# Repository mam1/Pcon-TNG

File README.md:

## PCON-TNG
------
### *** under construction and not stable ***
------
These are my notes on developing a multi channel programmable HVAC controller. The current iteration of the system is comprised of several ESP8266 modules, a BeagleBone Black (BBB), a BBB custom Control Cape and Digital IO Board(s) from Parallax. The system supports 16 channels.

A daemon (Dcon) is started as part of the boot process of the BeagleBone. The daemon decides if a channel should be on or off.  It does this by looking at a memory mapped file (ipc.dat). The memory mapped file creates a persistent space in virtual memory allowing processes to communicate.  It is maintained by a user interface process (Pcon).  Pcon is only active when a user is interacting with the system.  Temperature and humidity data is collected by ESP8266 modules. The ESP8266 modules read HDT22 sensors and use a wireless connection to post the data to the cloud (ThingSpeak) and to an Apache sever running on the BBB. A CGI on the BBB makes the data available to the daemon by updating shared memory and posts the data to a SQL database running on the Linux development machine.

A channel can be controlled by:

* time of day
* time of day and a sensor value
* manually

The BBB Control Cape (part of this project) maps 16 BeagleBone gpio pins to 2 2x10 pin headers.  Each header can drive 1 Parallax Digital IO board (DIOB).  It also connects 4 gpio pins to a heart beat display on the cape.

The Pcon application runs on the BBB.  It interacts with the daemon using shared memory.  Pcon provides a state machine driven user interface to configure channels, build and maintain schedules, query sensor and channel data, manually control channel states, etc.
- - - - - - - - -
#### Hardware
  * **BeagleBone Black Rev C - 4GB Flash, adafruit**
  * **BBB Control Cape**
    *  2 - 2 x 10 headers, DIOB control
            * Digital IO Board (DIOB), Sharp solid state relays part# S202S02F, Parallax
    *  4 - heart beat leds
  * **Wireless Sensors**
    * ESP8266 NodeMCU Dev Board, R2, Electro Dragon
    * DHT22 temperature/humidity sensor, Electro Dragon
    * 0.96” 128*64 OLED Display (i2c), Electro Dragon

##### BeagleBone GPIO assignments
                           {header,pin,gpio}
    * #define _CHAN0          {8,27,86}
    * #define _CHAN1          {8,28,88}
    * #define _CHAN2          {8,29,87}
    * #define _CHAN3          {8,30,89}
    * #define _CHAN4          {8,31,10}
    * #define _CHAN5          {8,32,11}
    * #define _CHAN6          {8,33,9}
    * #define _CHAN7          {8,34,81}
    * #define _CHAN8          {8,35,8}
    * #define _CHAN9          {8,36,80}
    * #define _CHAN10         {8,37,78}
    * #define _CHAN11         {8,38,79}
    * #define _CHAN12         {8,39,76}
    * #define _CHAN13         {8,40,77}
    * #define _CHAN14         {8,41,74}
    * #define _CHAN15         {8,42,75}
    * #define _HB0            {8,43,72}
    * #define _HB1            {8,44,73}
    * #define _HB2            {8,45,70}
    * #define _HB3            {8,46,71}

##### Parallel connection between BBB and DIOB(s)

#### Development Environment:

All code is stored on github.  The repository is cloned on two development machines.  At one site I have a Linux box running Mint 18.x and at the other I have have an iMac running OS X 10.10.x . The Bone is connected to my network. I can access it from either site using ssh. My makefiles use rsync to move the binaries from the development machines to the Bone as part of the build process. 

When cross compiling for the Bone on OS X I am using a tool chain I got from http://will-tm.com/cross-compiling-mac-os-x-mavericks. The only thing I needed to do was to create a case sensitive partition before copying the files from the .dmg file.  On the Linux box I tried installing a cross compile tool chain using the Mint software manager and experienced a lot of problems. After spending a lot of time dealing with missing files I gave up and installed the linaro-arm-linux-gnueabihf-4.9-2014.09_linux tool chain and it worked on the first try.

#### Language
* C - BBB
* Lua - ESP8266
* Bash Script
* Make

#### Envirnoment
* Development machines
	*	Mint 18.x - Intel Core i5-6600K 3.5GHz Quad-Core, Asus Z170-A ATX LGA1151 Motherboard Processor
	*	OS X 10.11.x - 3.4 GHz Intel Core i7 (iMac)
* BeagleBone Black (rev C)- Debian, jessie
* ESP8266 (nodeMCU dev board r2) - nodeMCU firmware 
* Communication
    *   MQTT broker (mosquitto) running on the BeagleBone

#### Channels and Schedules 
A channel is controlled by a schedule. There is a different schedule for each day of the week. Each channel has it own set of schedules. Channels 0-7 can switch a 60 volt 1.1 amp loads.  Channels 8 -15 can switch 120 volt 8 amp loads.  Each channel can be set manually to on or off.  Channels and also be controlled by time of day, i.e. on at 8:00 off at 14:30 or sensor value and time.  When a channel is controlled by time and sensor once a minute the remote sensor value is compared to the value stored in the schedule for current time and day of the week. If the actual values exceeds the schedule value the channel is turned off when. If the schedule values is less than the actual value the channel is turned on.  

##### Schedules:
A schedule is a list of times and corresponding states.  A channel that is controlled by time will be a list of times and states.  For example, a schedule of:

* 1:00  on
* 13:00 off

will result in the channel turning on at 1:00AM and off at 1:00PM.  If the current time is between 13:00 and 24:00 or between 0:0 and 13:00 the channel will be off.  Between 1:00 and 13:00 it will be on. While a schedule of:

* 1:00  off
* 13:00 on 

will result in the channel being off between 1:00 - 13:00. It will be on at any time before 1:00 or after 13:00.

* 1:00  on
* 13:00 off
* 18:00 on

will result in the channel turning on at 1:00, off at 13:00 and on at 18:00.  If the current time is between 1:00 and 13:00 the channel will be on, between 13:00 and 18:00 it will be off, between 18:00 and 0:0 it will be on and between 0:0 and 13:00 it will also be on.

#### MQTT
##### Topic structure:
topic = location1/location2/location3/command|sensor|status/text|float

#### Application Architecture
##### Interprocess Communication (BBB)
A memory mapped file is used to create a shared memory space in virtual memory.  This file contains communication, system, schedule and sensor data.  A daemon is started as part of the boot process on the BBB. If the daemon does not find the file it creates and initializes it.  Other processes can access this shared memory space.  Semaphores are used to control access to shared memory.
##### Processes
A daemon (Dcon) running on the BBB communicates with the DIOB(s).  It uses data located in a memory mapped file (ipc.dat) and the real time clock to determine the state of each channel. The state of each channel is reset once every minute. The daemon does not require any other processes to be active.

A second daemon (mqtt-watcher) running on the BBB connects to a mqtt broker also running on the BBB.  The daemon subscribes to a high level topic and listens for any message.  It parses the topic and takes appropriate action.

A command processor (Pcon) is the user interface to the system.  It allows the user to modify the data in shared memory.

ESP8266 modules run independently of other system components.  Each module posts its sensor readings to an Apache web server running on the BBB.  A CGI (Scon) loads the readings into  shared memory. 
##### Command Processor
The command processor is the most complex part of this project. 

The use of unbuffered input allows the application to mediately react to the press of the ECS key, but it requires that the command processor handle the arrow and delete keys. The command processor maintains a buffer which matches the user's screen. The process loops waiting for a character to be detected.  ESC, Del, up_arrow, down_arrow, left_arrow and right_arrow are handled directly.  An ESC will clear all buffers and reset both state machines.  The delete and arrow commands work as they do on the command line. Any other character is passed to the first state machine (char_fsm).  It parses the input stream into tokens and pushes them on to FIFO stack.  A CR will cause char_fsm to pass the stack of tokes to the command processor.  

The command processor pops tokens off the stack and feeds them to a second fsm (cmd_fsm).  It takes some action based on the token.  If more input is required it is popped off the stack, if present, or the user is prompted. This continues until the stack is empty. Then the command processor lets the cms_fsm know there is no more input then continues the main loop, waiting for user input. 

When the main event loop detects a non-empty token stack it passes the stack to a second state machine (cmd_fsm) which processes the token stack.

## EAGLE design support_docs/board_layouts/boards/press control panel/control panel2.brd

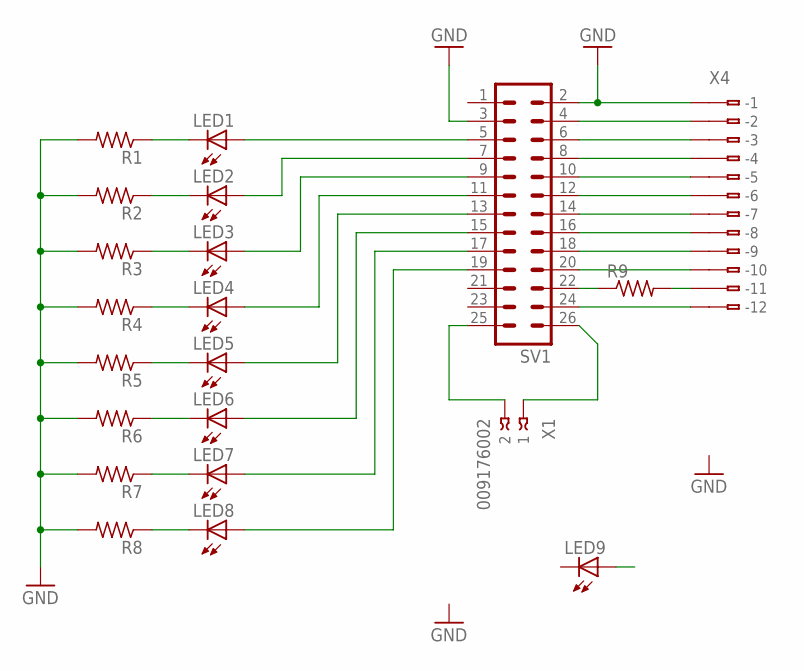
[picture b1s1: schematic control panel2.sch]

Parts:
LED1, LED2, LED3, LED4, LED5, LED6, LED7, LED8, LED9: LED3MM
R1, R2, R3, R4, R5, R6, R7, R8: R-US_0309/V; 0309V
R9: R-US_0204/7; 0204/7
SV1: MA13-2
X1: 009176002
X4: 233-212

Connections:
GND: R1.2, R2.2, R3.2, R4.2, R5.2, R6.2, R7.2, R8.2, SV1.2, SV1.3, X4.B1 (B-1)
unnamed: LED1.A, SV1.5
unnamed: LED2.A, SV1.7
unnamed: LED3.A, SV1.9
unnamed: LED4.A, SV1.11
unnamed: LED5.A, SV1.13
unnamed: LED6.A, SV1.15
unnamed: LED7.A, SV1.17
unnamed: LED8.A, SV1.19
unnamed: LED1.K (C), R1.1
unnamed: LED2.K (C), R2.1
unnamed: LED3.K (C), R3.1
unnamed: LED4.K (C), R4.1
unnamed: LED5.K (C), R5.1
unnamed: LED6.K (C), R6.1
unnamed: LED7.K (C), R7.1
unnamed: LED8.K (C), R8.1
unnamed: SV1.24, X4.B12 (B-12)
unnamed: SV1.4, X4.B2 (B-2)
unnamed: SV1.6, X4.B3 (B-3)
unnamed: SV1.8, X4.B4 (B-4)
unnamed: SV1.10, X4.B5 (B-5)
unnamed: SV1.12, X4.B6 (B-6)
unnamed: SV1.14, X4.B7 (B-7)
unnamed: SV1.16, X4.B8 (B-8)
unnamed: SV1.25, X1.2
unnamed: SV1.26, X1.1
unnamed: SV1.18, X4.B9 (B-9)
unnamed: SV1.20, X4.B10 (B-10)
unnamed: R9.1, SV1.22
unnamed: R9.2, X4.B11 (B-11)

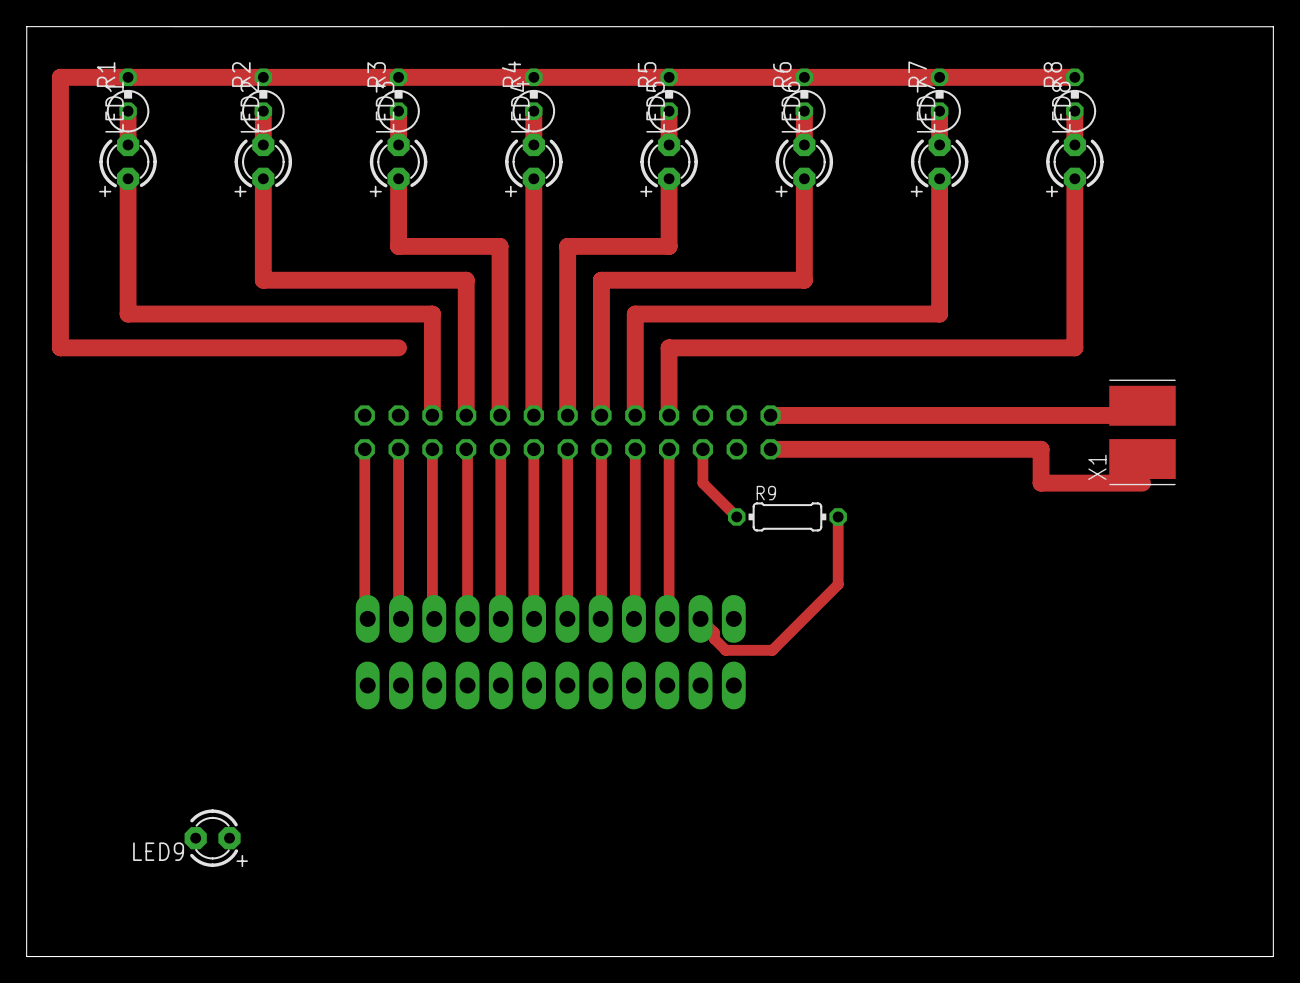
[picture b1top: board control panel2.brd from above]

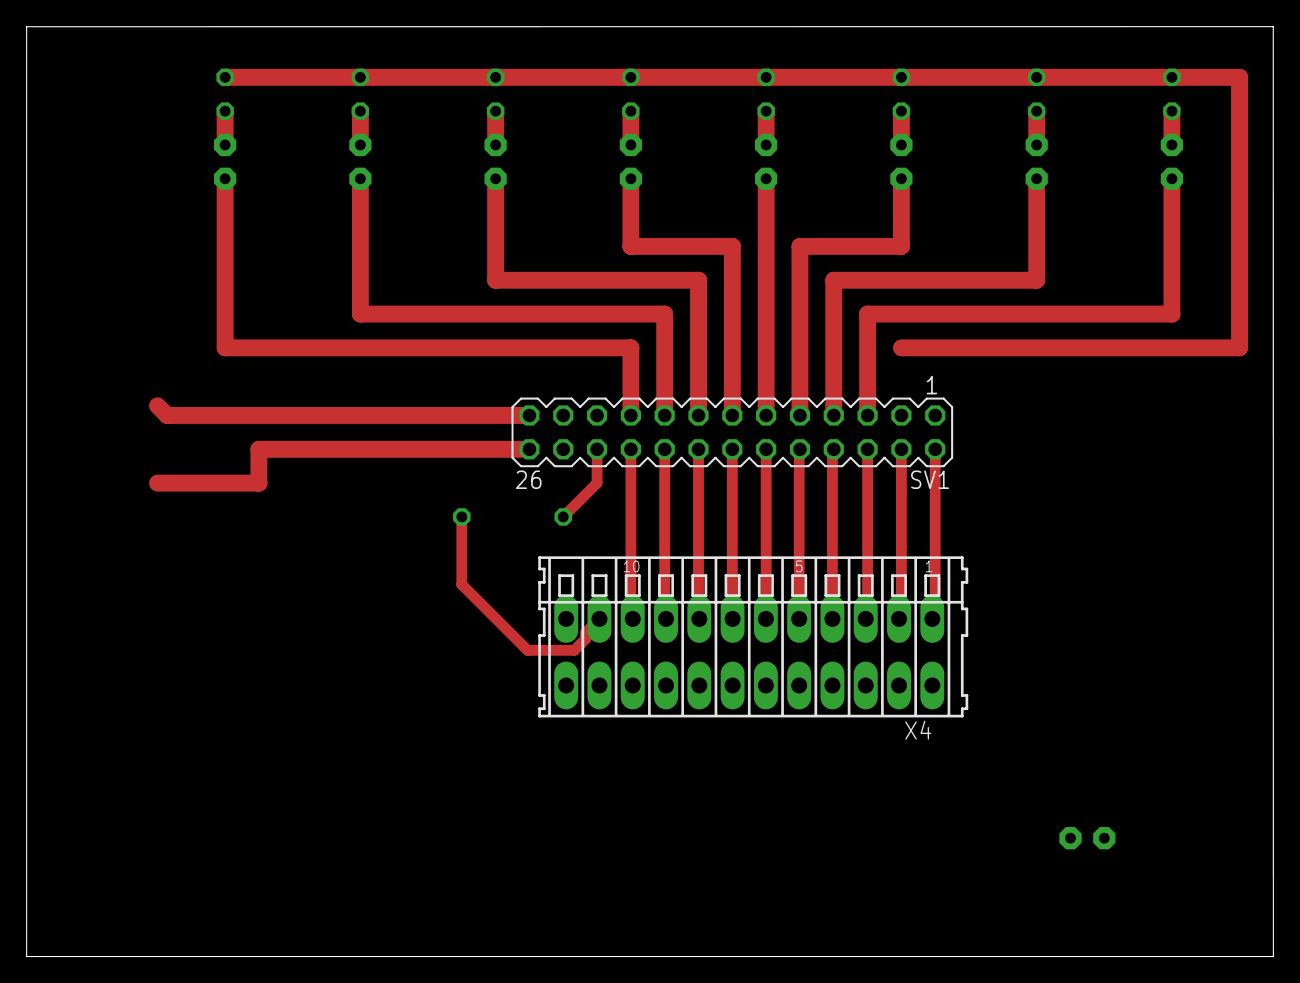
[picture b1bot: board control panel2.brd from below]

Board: 2 copper layers, 93.7 x 69.9 mm, 21 parts (2 on the bottom side), 31 nets.

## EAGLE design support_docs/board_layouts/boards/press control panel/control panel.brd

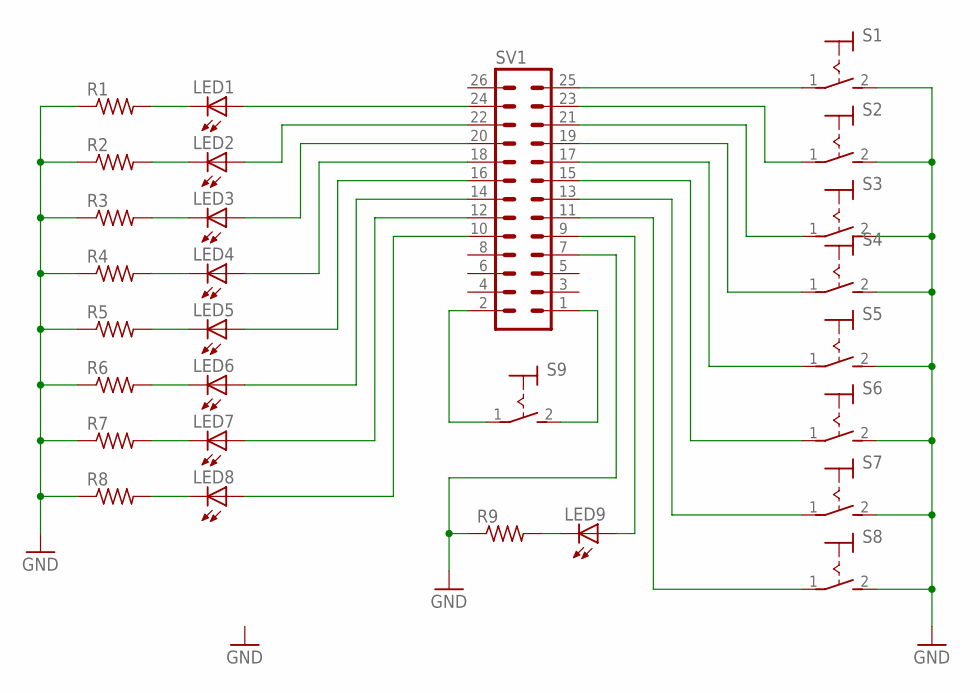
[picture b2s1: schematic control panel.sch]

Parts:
LED1, LED2, LED3, LED4, LED5, LED6, LED7, LED8, LED9: LED3MM
R1, R2, R3, R4, R5, R6, R7, R8, R9: R-US_0309/12; 0309/12
S1, S2, S3, S4, S5, S6, S7, S8, S9: MS243
SV1: MA13-2

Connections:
GND: R1.1, R2.1, R3.1, R4.1, R5.1, R6.1, R7.1, R8.1, R9.1, S1.2 (S), S2.2 (S), S3.2 (S), S4.2 (S), S5.2 (S), S6.2 (S), S7.2 (S), S8.2 (S), SV1.7, SV1.8
unnamed: LED1.A, SV1.24
unnamed: LED2.A, SV1.22
unnamed: LED3.A, SV1.20
unnamed: LED4.A, SV1.18
unnamed: LED5.A, SV1.16
unnamed: LED6.A, SV1.14
unnamed: LED7.A, SV1.12
unnamed: LED8.A, SV1.10
unnamed: LED1.K (C), R1.2
unnamed: LED2.K (C), R2.2
unnamed: LED3.K (C), R3.2
unnamed: LED4.K (C), R4.2
unnamed: LED5.K (C), R5.2
unnamed: LED6.K (C), R6.2
unnamed: LED7.K (C), R7.2
unnamed: LED8.K (C), R8.2
unnamed: S1.1, SV1.25
unnamed: S2.1, SV1.23
unnamed: S3.1, SV1.21
unnamed: S4.1, SV1.19
unnamed: S5.1, SV1.17
unnamed: S6.1, SV1.15
unnamed: S7.1, SV1.13
unnamed: S8.1, SV1.11
unnamed: S9.1, SV1.2
unnamed: S9.2 (S), SV1.1
unnamed: LED9.A, SV1.9
unnamed: LED9.K (C), R9.2

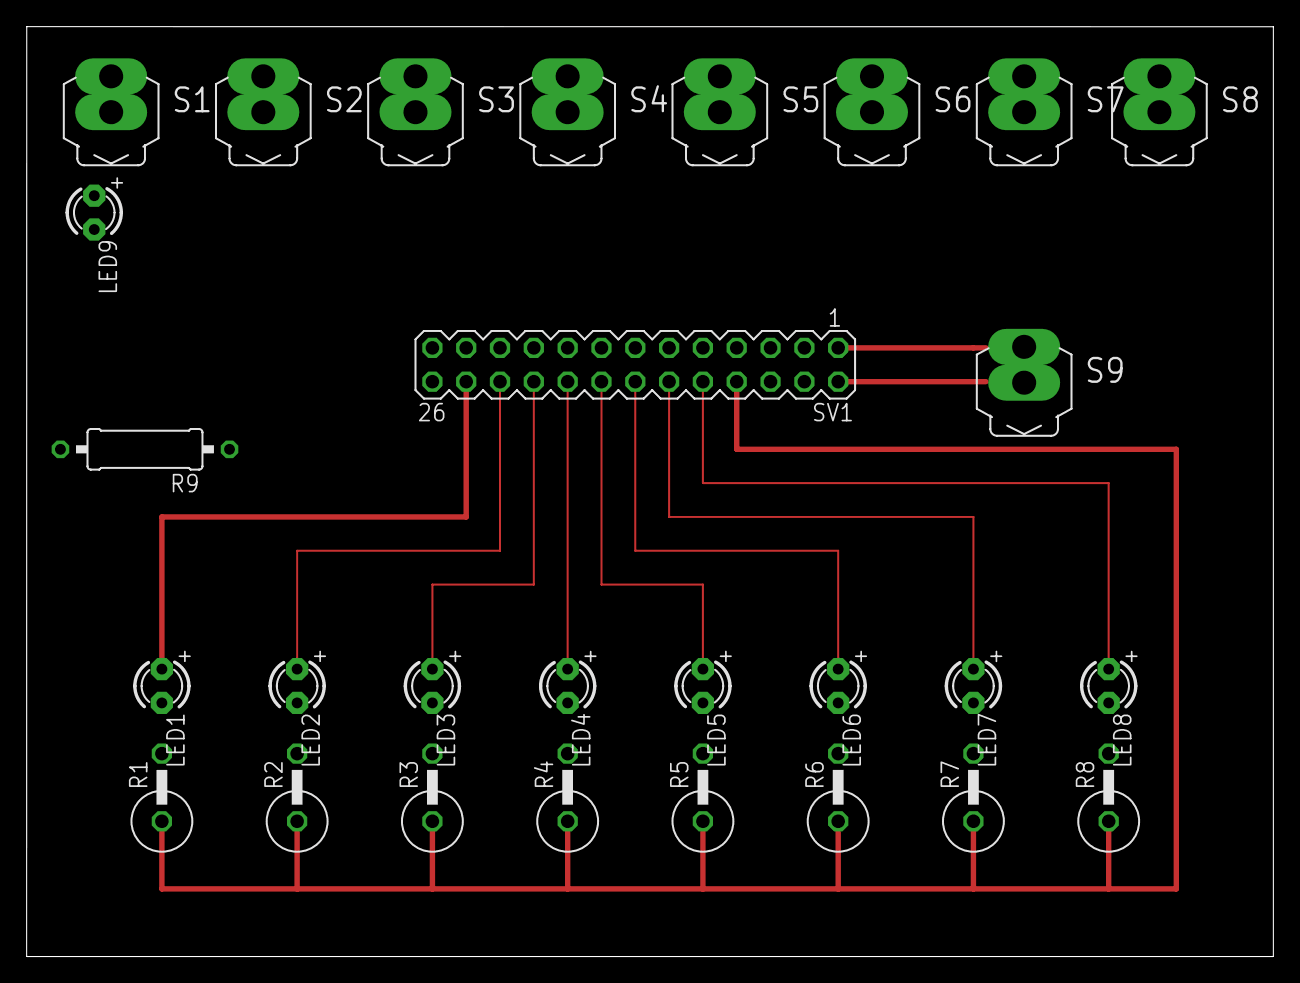
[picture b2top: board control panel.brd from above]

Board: 2 copper layers, 93.7 x 69.9 mm, 28 parts (0 on the bottom side), 29 nets.

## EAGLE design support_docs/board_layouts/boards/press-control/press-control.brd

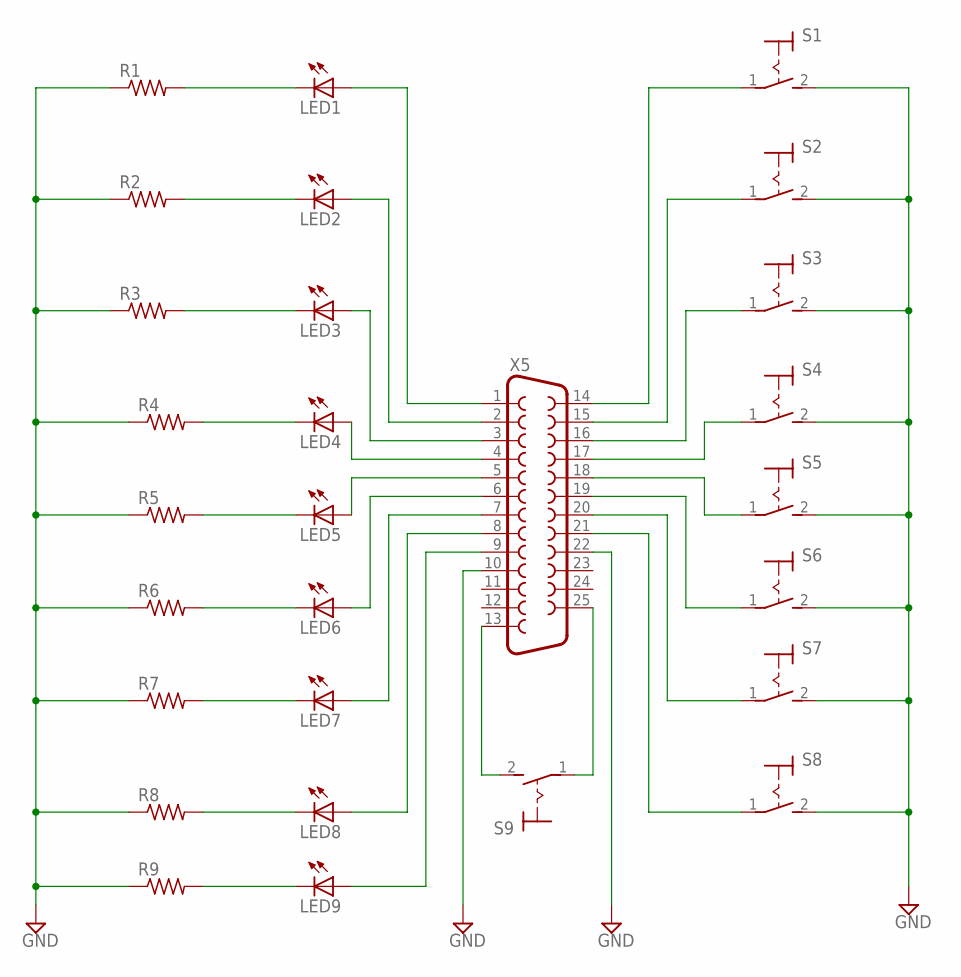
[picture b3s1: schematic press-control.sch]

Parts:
LED1, LED2, LED3, LED4, LED5, LED6, LED7, LED8, LED9: LED5MM
R1, R2, R3, R4, R5, R6, R7, R8, R9: R-US_0207/10; 0207/10
S1, S2, S3, S4, S5, S6, S7, S8, S9: MS243
X5: DB25_FEMALEV; F25V

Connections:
GND: R1.1, R2.1, R3.1, R4.1, R5.1, R6.1, R7.1, R8.1, R9.1, S1.2 (S), S2.2 (S), S3.2 (S), S4.2 (S), S5.2 (S), S6.2 (S), S7.2 (S), S8.2 (S), X5.10, X5.22
unnamed: LED1.K (C), R1.2
unnamed: LED2.K (C), R2.2
unnamed: LED3.K (C), R3.2
unnamed: LED4.K (C), R4.2
unnamed: LED5.K (C), R5.2
unnamed: LED6.K (C), R6.2
unnamed: LED7.K (C), R7.2
unnamed: LED8.K (C), R8.2
unnamed: LED4.A, X5.4
unnamed: LED5.A, X5.5
unnamed: LED3.A, X5.3
unnamed: LED2.A, X5.2
unnamed: LED1.A, X5.1
unnamed: LED6.A, X5.6
unnamed: LED7.A, X5.7
unnamed: LED8.A, X5.8
unnamed: S5.1, X5.18
unnamed: S4.1, X5.17
unnamed: S3.1, X5.16
unnamed: S2.1, X5.15
unnamed: S1.1, X5.14
unnamed: S6.1, X5.19
unnamed: S7.1, X5.20
unnamed: S8.1, X5.21
unnamed: S9.2 (S), X5.13
unnamed: S9.1, X5.25
unnamed: LED9.A, X5.9
unnamed: LED9.K (C), R9.2

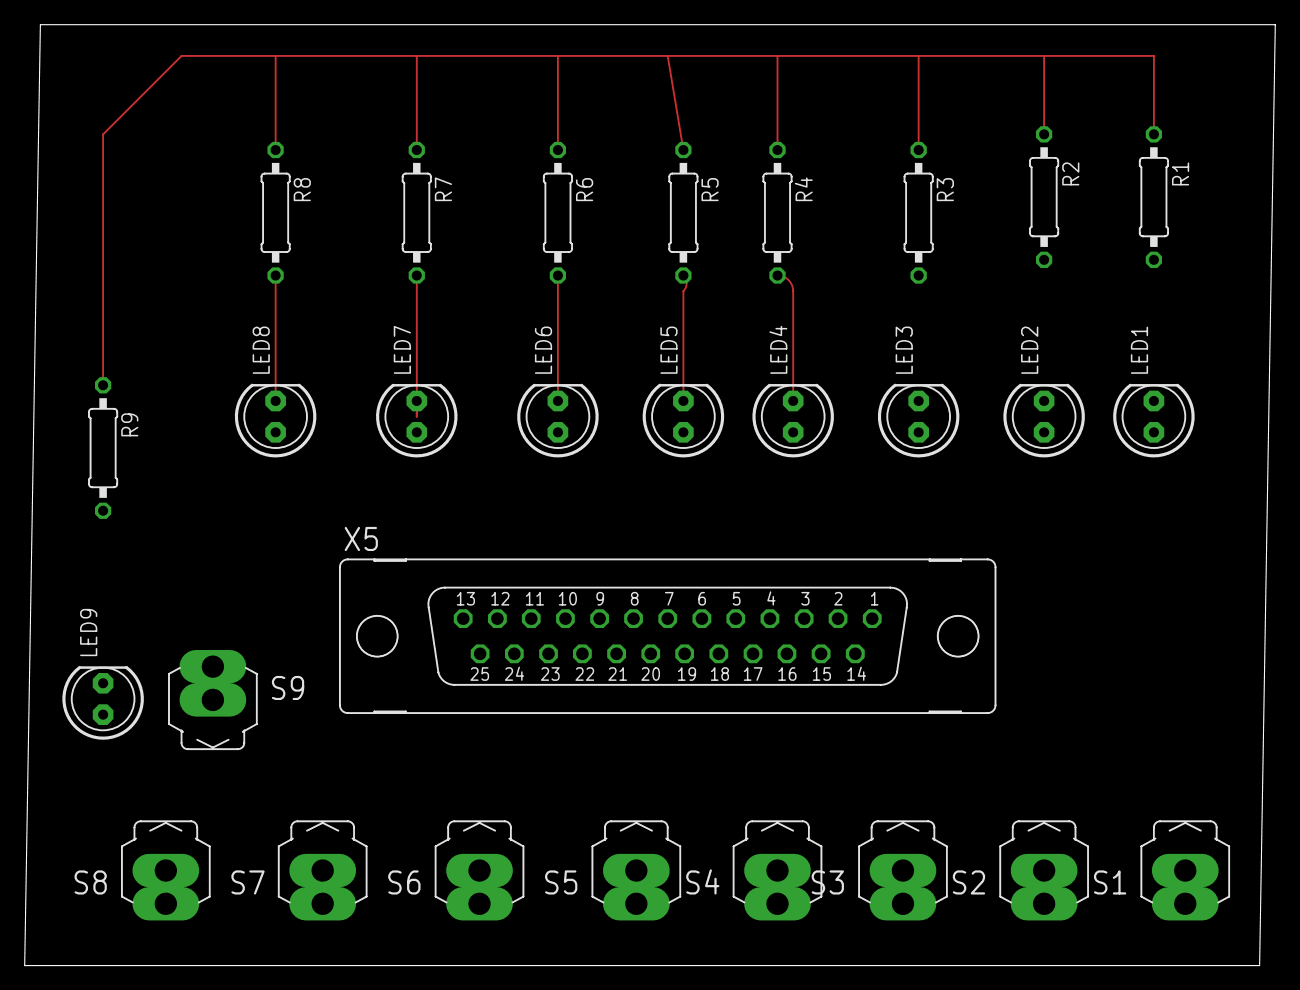
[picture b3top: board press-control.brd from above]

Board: 2 copper layers, 101.3 x 76.2 mm, 28 parts (0 on the bottom side), 29 nets.

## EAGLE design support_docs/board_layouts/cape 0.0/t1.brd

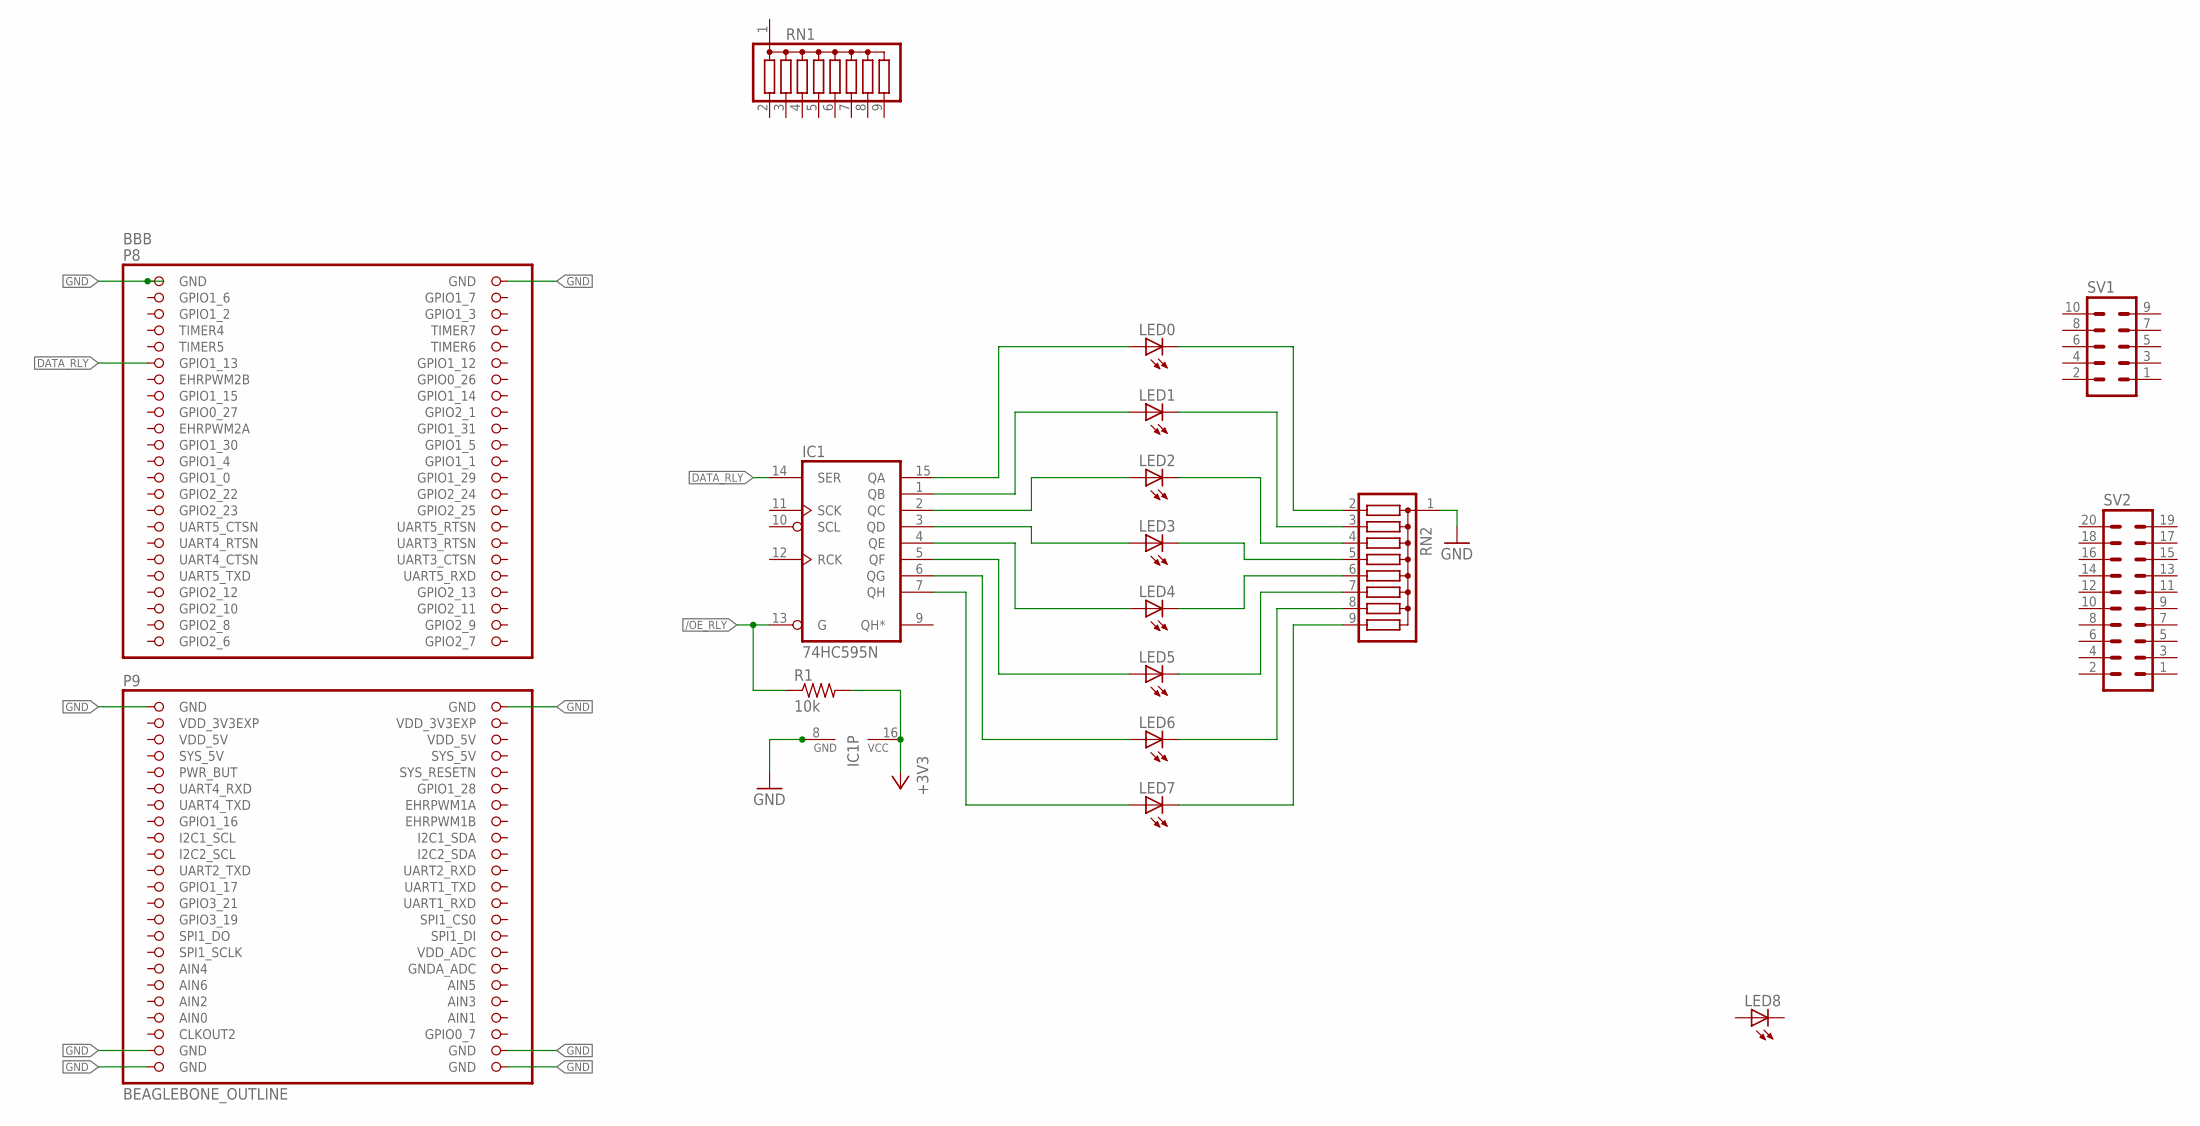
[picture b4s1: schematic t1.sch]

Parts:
BBB: BEAGLEBONE_OUTLINE; BEAGLEBONE_SHIELD
IC1: 74HC595N; DIL16
LED0, LED1, LED2, LED3, LED4, LED5, LED6, LED7, LED8: LED3MM
R1: 10k; 0207/12
RN1, RN2: G08R; SIL9
SV1: MA05-2
SV2: MA10-2

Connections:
+3V3: IC1.16 (VCC), R1.2
/OE_RLY: IC1.13 (G), R1.1
AIN0: BBB.85 (AIN0)
DATA_RLY: BBB.11 (GPIO1_13), IC1.14 (SER)
GND: BBB.1 (GND), BBB.2 (GND), BBB.47 (GND), BBB.48 (GND), BBB.89 (GND), BBB.90 (GND), BBB.91 (GND), BBB.92 (GND), IC1.8 (GND), RN2.1
unnamed: LED7.K (C), RN2.9
unnamed: LED1.K (C), RN2.3
unnamed: LED3.K (C), RN2.5
unnamed: LED2.K (C), RN2.4
unnamed: LED4.K (C), RN2.6
unnamed: LED6.K (C), RN2.8
unnamed: LED0.K (C), RN2.2
unnamed: IC1.15 (QA), LED0.A
unnamed: IC1.1 (QB), LED1.A
unnamed: LED5.K (C), RN2.7
unnamed: IC1.2 (QC), LED2.A
unnamed: IC1.3 (QD), LED3.A
unnamed: IC1.4 (QE), LED4.A
unnamed: IC1.5 (QF), LED5.A
unnamed: IC1.6 (QG), LED6.A
unnamed: IC1.7 (QH), LED7.A
SYS_5V: BBB.53 (SYS_5V)
VDD_3V3EXP: BBB.49 (VDD_3V3EXP), BBB.50 (VDD_3V3EXP)
VDD_5V: BBB.51 (VDD_5V), BBB.52 (VDD_5V)

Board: 2 copper layers, 16 parts (0 on the bottom side), 22 nets, no tracks yet.

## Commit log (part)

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2017-01-10 modify stats diagram for save/load/delete shared memory
2017-01-11 save/restor shared memory working
2017-01-11 cleaned up set commands
2017-01-11 seems to be working correctly
2017-01-18 got the CGI working
2017-01-18 add header file for Scon version numbers
2017-01-18 up version numbers before next system test
2017-01-18 added more text to startup
2017-01-20 working on script-lib makefile
2017-01-20 script_lib Makefile fixed
2017-01-20 ask to kill running daemon on UI startup
2017-01-20 remove startit copy
2017-01-20 Scon fixed warning messsages, make fixed to work from either os
2017-01-20 up version number, ready for system test
2017-01-20 Dcon version 2.3.0, warning messaes fixed, ready for system test
2017-01-21 moving to barn
2017-01-21 keep lock on shared memory longer
2017-01-22 added second try on open sensor log
2017-01-25 broke cmd_fsm.c
2017-01-25 grab command is not working
2017-01-28 script to copy sendor log under construction
2017-01-28 working on setup development env for Mint box
2017-01-29 addd code to process sensor log data
2017-01-31 adding auto restart and interupt abort
2017-01-31 new sensor log processing code running on Mint box
2017-02-02 fixed problem with ESP8266 aquiring IP
2017-02-04 add oled support
2017-02-05 new ESP8266 code, change to float
2017-02-05 add heart beat flash to oled
2017-02-05 heart beat display working
2017-02-05 handeling floaing point temp and humidity correctly
2017-02-05 convering sensor data log to float
2017-02-06 sensor data log converted to float
2017-02-07 help cleaned up for states 0,4,13
2017-02-07 fixed sensor display in cmd_fsm
2017-02-07 multipal sensors working
2017-02-07 add data structures for senor linked list
2017-02-08 ready to add new states to handle sensor list maint
2017-02-08 add new sensor
2017-02-08 up version to 1.2.0
2017-02-08 update for sensor maint
2017-02-08 increased the size of the state tables
2017-02-09 adding code to maitian sensor list
2017-02-09 revise senor maint part of fsm
2017-02-09 add senor maint code, not tested
2017-02-10 investigating buffer overflow on input strings >30 char
2017-02-10 chasing problem with input buffer overflow
2017-02-11 still overflowing input
2017-02-12 process-master working
2017-02-12 add min temp code
2017-02-12 add last update code
2017-02-12 last update code working
2017-02-12 add record cont display
2017-02-12 last update working
2017-03-02 messing with shell scripts
2017-03-02 playing with formating
2017-03-03 script_lib maek working for Mint
2017-03-04 pushing externasl ip address to Dropbox
2017-03-05 one more tst
2017-03-05 add loging" git push
2017-03-06 pushing data to dropbox
2017-03-07 trying to save this work from a bad merge
2017-03-07 cron pullit not working
2017-03-07 change to pullit
2017-03-07 chasing bugs no progress
2017-03-08 pullit not working right
2017-03-08 pullit and process are working, crontab set to once a day
2017-03-08 messing with command buff, overflow?
2017-03-09 reconnect VPN if necessary
2017-03-09 looking good up version to 2.0.0
2017-03-09 add check to see if the vpn realy connected
2017-03-09 add 1 to second index of cmd_buffer
2017-03-09 adding down arrow code
2017-03-11 getting read to work on new master format
2017-03-13 dummy
2017-03-13 confused
2017-03-13 working on make files for addinf mySQL
2017-03-14 added vpn status to log
2017-03-17 switching system clock for rtc
2017-03-18 rtc updated from system clock, working
2017-03-18 changing seror time stamp to unix epoch
2017-03-18 modify process.c to use time_t time
2017-03-19 Scon clean compile ater changing to time_t
2017-03-21 change to accomadate time_t data staructure
2017-03-23 change the daemon to system time in place of rtc
2017-03-25 fixed formating
2017-03-26 messed up from change to time_t
2017-03-27 schedules not right
2017-03-27 still dealing with time_t
2017-03-27 command buffer working correctly
2017-03-27 working on schedule set
2017-03-27 new directory locations broke pullit
2017-03-27 modify to allow more than on bone
2017-03-29 trash achive
2017-03-29 working on load script
2017-03-31 changes to support nre bone nad cape
2017-03-31 getting the scripts to work with the sencond bone
2017-04-01 changes to support second bone
2017-04-02 adding new cap design
2017-04-02 schedules are still messed up
2017-04-02 schedules are getting better
2017-04-03 OSX load script not working
2017-04-03 Pcon system status scrip working
2017-04-04 fixed cmd ring buffer
2017-04-04 schedule maint working
2017-04-04 up version 10.10.0
2017-04-04 add directory for scripts that can be run on either OSX or Mint
2017-04-04 add DIOB docs
2017-04-05 new cape design
2017-04-05 schedule contron working better but not right
2017-04-06 schedule maint seems to be workng corectely
2017-04-06 new version of status script
2017-04-06 fixed schedule bug
2017-04-06 10.11.0 1 and 2 record schedules working correctly
2017-04-06 schedules with >3 recornds working
2017-04-07 cleaned up some help messages
2017-04-07 still getting segmentation fault with long commands
2017-04-13 new script to lonin to remote bones
2017-04-13 cleaning up scripts
2017-04-13 base line before next test series
2017-04-13 still crashinf on long tokens
2017-04-14 still crashing on long input
2017-04-16 turning off trace fixed the long token buffer overflow problem
2017-04-16 fixed most complier warings
2017-04-16 remove debug printf(s)
2017-04-16 remove rtc set and replace with sedit
2017-04-17 sensor maint working, needs cleanup
2017-04-17 sedit still needs work
2017-04-18 working on sedit
2017-04-18 make lib
2017-04-24 formating sensor list output, looking good
2017-04-29 moving to shop
2017-04-29 add backup script
2017-05-01 change for new directory layout on ShopMint
2017-05-02 working on sensor data display
2017-05-02 addiing proper deamon launch
2017-05-03 adjust script for new directtory structure
2017-05-03 working on deamizing Dcon
2017-05-04 crosss compile broken on ShopMint
2017-05-04 cleaning up daemon
2017-05-05 reinstall cross compiler on ShopMint
2017-05-07 segmentation fault showed up
2017-05-07 staritn on cape desigh design
2017-05-07 test all gpio pins
2017-05-07 switch beaglebone images
2017-05-07 move to house
2017-05-08 new io lib
2017-05-08 switched to new io lib
2017-05-08 new io lib working
2017-05-11 trying to accesss HDMI pins
2017-05-14 can not access HDMI pins
2017-05-14 needs to be modified to become a service
2017-05-14 controling pind by calling shell command <config-pin>
2017-05-15 found 16 working gpio pins
2017-05-15 daemon using cofig-pin to controll gpio pins
2017-05-15 daemon working with config-pin, all 16 channels
2017-05-15 clean up log entries
2017-05-15 remove commented out code
2017-05-16 working of conversion to service
2017-05-22 woring with new way to access GPIOs
2017-05-22 working
2017-05-23 new cape layout
2017-05-30 messing with oerlays
2017-05-31 testing
2017-06-01 deamon converted to use overlay gpio control
2017-06-01 damemon looking good
2017-06-02 track Dcon binary
2017-06-04 geting Dcon to work with systemctl, start script works
2017-06-05 auto start od deamon working
2017-06-05 change to match current code
2017-06-15 back up script working
2017-06-15 Dcon bin tracked
2017-06-18 assign static IP to bones
2017-06-30 add scripts to sav/restore sdcard images
2017-07-04 handle arrow keys
2017-07-07 insert working
2017-07-16 add ring bufer
2017-07-16 ring buffer working
2017-07-16 character delete working
2017-10-24 messing with eagle files
2017-10-30 tin working correctly
2017-10-30 test new branch
2017-10-30 broken
2017-10-30 getting closer
2017-10-30 still messed up
2017-10-31 clean up
2017-10-31 still broken
2017-11-01 add flow chart for Pcon
2017-11-02 working on flow chart
2017-11-03 new Pcon design looks good
2017-11-03 messing with Pcon
2017-11-04 refactoring Pcon
2017-11-09 messing with pcb layout
2017-11-09 command entry works
2017-11-10 getting better
2017-11-12 refactoring Pcon code to match flow chart
2017-11-12 up arrow working
2017-11-12 clean up flow
2017-11-13 add Pcon flow chart to readme file
2017-11-18 fix ring buffer duplicates
2017-11-19 delete/insert working
2017-11-20 version 13.4.3 ready to relace master
2017-11-20 press-control board
2017-11-21 add show/hide channel data
2017-11-21 pin assignments changed to match old dauwire wrap cape
2017-11-22 v1.0 running bays
2017-11-22 up version numbers
2017-11-22 setting up bones with static IPs and makeing the make files match
2017-11-22 move to barn
2017-11-22 back to the house
2017-11-24 clean up overview
2017-11-25 working on delete
2017-11-25 working on delete problem
2017-11-26 improve description
2017-11-27 working of press controller schmatic
2017-11-27 fixed error handling of channel number out od range
2017-11-28 tag v1.1
2017-11-29 moving to the barn
2017-11-29 v1.2 ready to move to production
2017-11-29 clean up load scripts to match statis IPs
2017-11-29 improve load scripts
2017-11-29 add support for prod and dev host names
2017-11-29 fix support for prod and dev host names
2017-11-29 starting to look at the sensor support
2017-11-30 fix merge
2017-11-30 cleaning up sensor support code
2017-12-01 trying to test CGI
2017-12-02 trying to get CGI working
2017-12-03 working on CGI
2017-12-03 workinf with new sdk for ESP8266
2017-12-04 cleaned up prompt for state 0
2017-12-05 continue to clean up prompting
2017-12-08 ignor .bin files
2017-12-08 track the Pcon binary
2017-12-09 clean up contimues
2017-12-09 fixed some schedule edit prompt issues
2017-12-10 redesign - not enough io pins
2017-12-10 CGI working
2017-12-10 load production machine
2017-12-11 CGI working with no apache2 errors
2017-12-13 archive script partially working
2017-12-18 code to display sensor vvalues working
2017-12-19 updating sensor code on the ESP8266s
2017-12-21 slist working in state 0
2017-12-23 back to house, cmd_fsm broken
2017-12-25 archive not working
2017-12-25 sort is still not working
2017-12-28 beter but still has problems
2017-12-31 adding code to push sensor reading to dropbox
2017-12-31 Add sensor data push to push_ip
2018-01-01 sensor upload working
2018-02-21 new board design
2018-02-22 new control panel board
2018-02-25 messing with Eagle
2018-03-14 new design
2018-04-12 add led control
2018-04-18 add board for main controler
2018-07-28 edit board layout
2018-07-28 left on house machine
2018-08-03 change relay pin assignments
2018-08-03 messing with pin assignments
2018-08-03 configured for 7 channels
2018-08-03 production load 7 channel config
2018-08-04 new version of gpio test"
2018-08-04 change ip
2018-08-04 clean compile
2018-08-06 change gpio initalization
2018-08-06 new make for system build
2018-08-06 new ip adresses
2018-08-07 new login script
2018-08-08 not sure what changed
2018-08-08 fix comments
2018-08-08 convert to mastermake
2018-08-08 make working on Mint
2018-08-09 changes to comments
2018-08-09 still working on build system
2018-08-10 add delay after turning channel on
2018-08-10 work on build system
2018-11-08 add docs
2018-11-11 implementing MQTT
2018-11-11 adding MQTT
2018-11-13 mqtt implemented on esp8266 sensors
2018-11-17 improve sensor code
2019-11-06 get daemon compile working
2019-11-07 moving to house
2019-11-07 closer
2019-11-10 cross compile not working
2019-11-13 not working
2019-11-13 still 64 bit
2019-11-14 xcompile not working
2019-11-14 compile workimng
2019-11-14 xcompile working
2019-11-14 Pcon running working on daemon
2019-11-15 Pcon and Dcon running
2019-11-16 add second daemon
2019-11-16 before messing with IPC data structure
2019-11-17 refactoring daemons
2019-11-20 working on it
2019-12-01 xcompile mqtt not working
2019-12-08 still not working
2020-02-25 initial setup
2020-02-27 example working
2020-02-27 subscribe working
2020-02-29 starting parce
2020-02-29 parcer working
2020-03-01 back to the barn
2020-03-01 back to house
2020-03-01 fifo quue working
2020-03-01 debugging fifo q
2020-03-04 geting closer
2020-03-07 not finding bottom of q
2020-03-07 no progress
2020-03-08 linked list working correctly
2020-03-08 working on cross compile
2020-03-10 mqtt subscribr working
2020-03-10 reading mqtt messages
2020-03-12 new daemon archetecture
2020-03-13 new daemons

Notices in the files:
parts and their libraries:
SparkFun-Retired: Licensing: Creative Commons ShareAlike 4.0 International - https://creativecommons.org/licenses/by-sa/4.0
